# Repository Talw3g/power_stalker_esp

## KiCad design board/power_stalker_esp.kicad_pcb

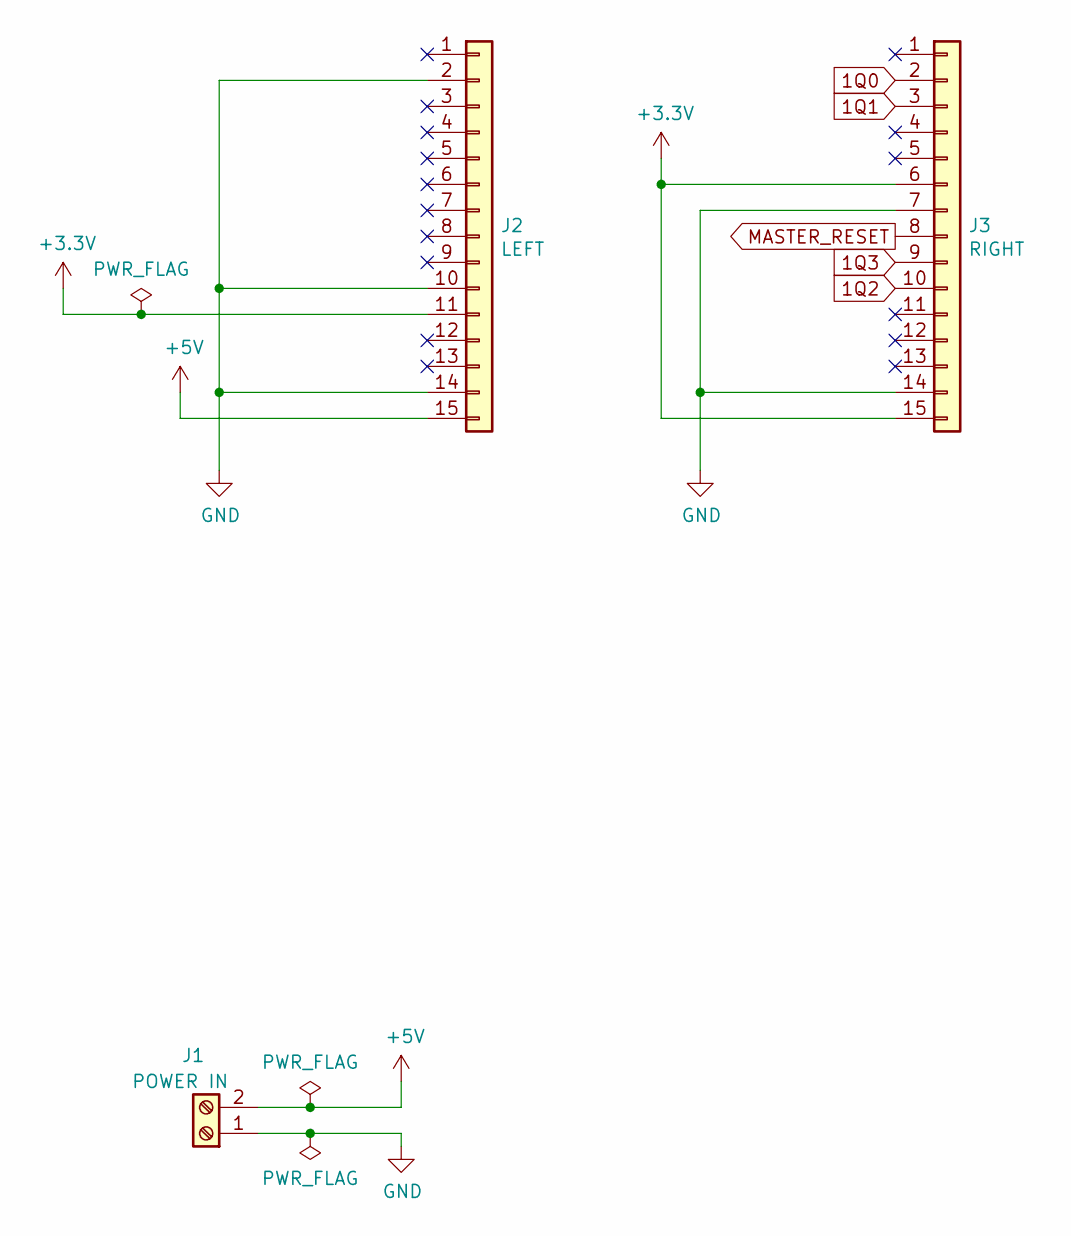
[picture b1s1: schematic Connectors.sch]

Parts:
J1: POWER IN; mpt_0,5-2-2,54; Farnell 3041359
J2: LEFT; PinSocket_1x15_P2.54mm_Vertical; Farnell 2779587
J3: RIGHT; PinSocket_1x15_P2.54mm_Vertical; Farnell 2779587

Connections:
1Q0: J3.2; also elsewhere on the board
1Q1: J3.3; also elsewhere on the board
1Q2: J3.10; also elsewhere on the board
1Q3: J3.9; also elsewhere on the board
+3V3: J2.11, J3.6, J3.15; also elsewhere on the board
+5V: J1.2, J2.15
GND: J1.1, J2.2, J2.10, J2.14, J3.7, J3.14; also elsewhere on the board
MASTER_RESET: J3.8; also elsewhere on the board

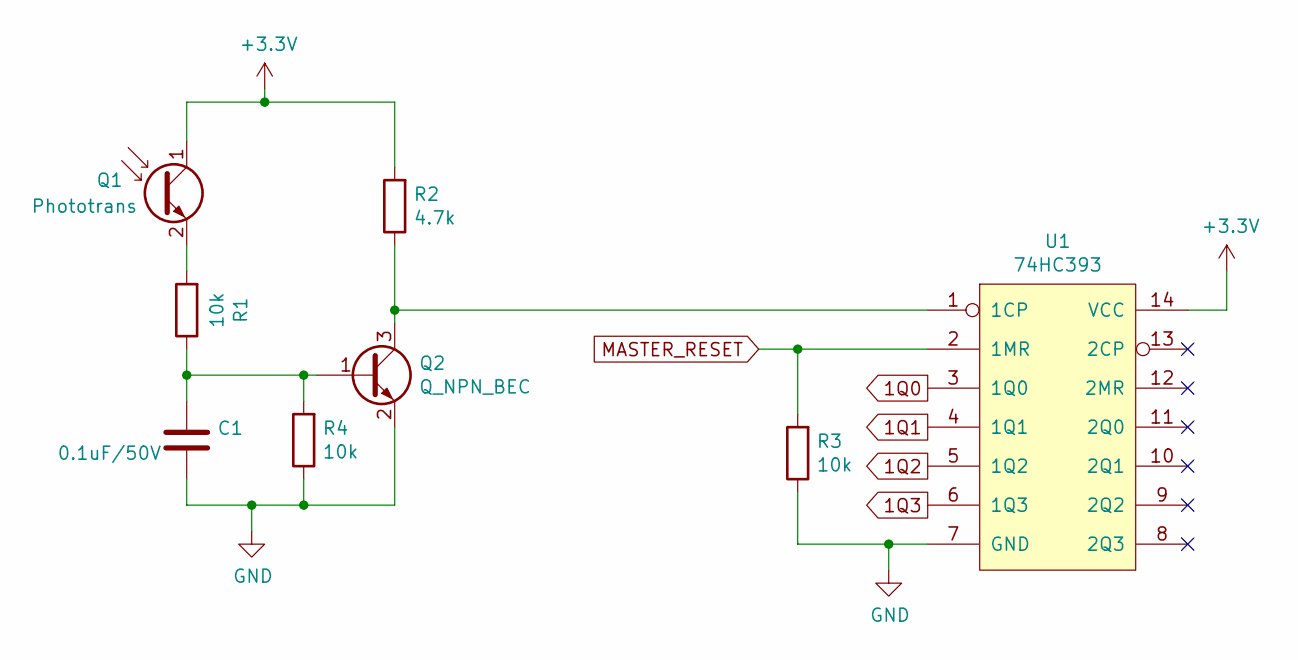
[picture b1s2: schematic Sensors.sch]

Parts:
C1: 0.1uF/50V; C_0603_1608Metric_Pad1.05x0.95mm_HandSolder
Q1: Phototrans; mpt_0,5-2-2,54; Farnell 1497675
Q2: Q_NPN_BEC; SOT-23; Farnell 2464062
R1, R3, R4: 10k; R_0603_1608Metric_Pad1.05x0.95mm_HandSolder
R2: 4.7k; R_0603_1608Metric_Pad1.05x0.95mm_HandSolder
U1: 74HC393; SOIC-14_3.9x8.7mm_P1.27mm; Farnell 1085344

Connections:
1Q0: U1.3 (1Q0); also elsewhere on the board
1Q1: U1.4 (1Q1); also elsewhere on the board
1Q2: U1.5 (1Q2); also elsewhere on the board
1Q3: U1.6 (1Q3); also elsewhere on the board
+3V3: Q1.1 (C), R2.2, U1.14 (VCC); also elsewhere on the board
GND: C1.2, Q2.2 (E), R3.1, R4.1, U1.7 (GND); also elsewhere on the board
MASTER_RESET: R3.2, U1.2 (1MR); also elsewhere on the board
unnamed: C1.1, Q2.1 (B), R1.1, R4.2
unnamed: Q1.2 (E), R1.2
unnamed: Q2.3 (C), R2.1, U1.1 (1CP)

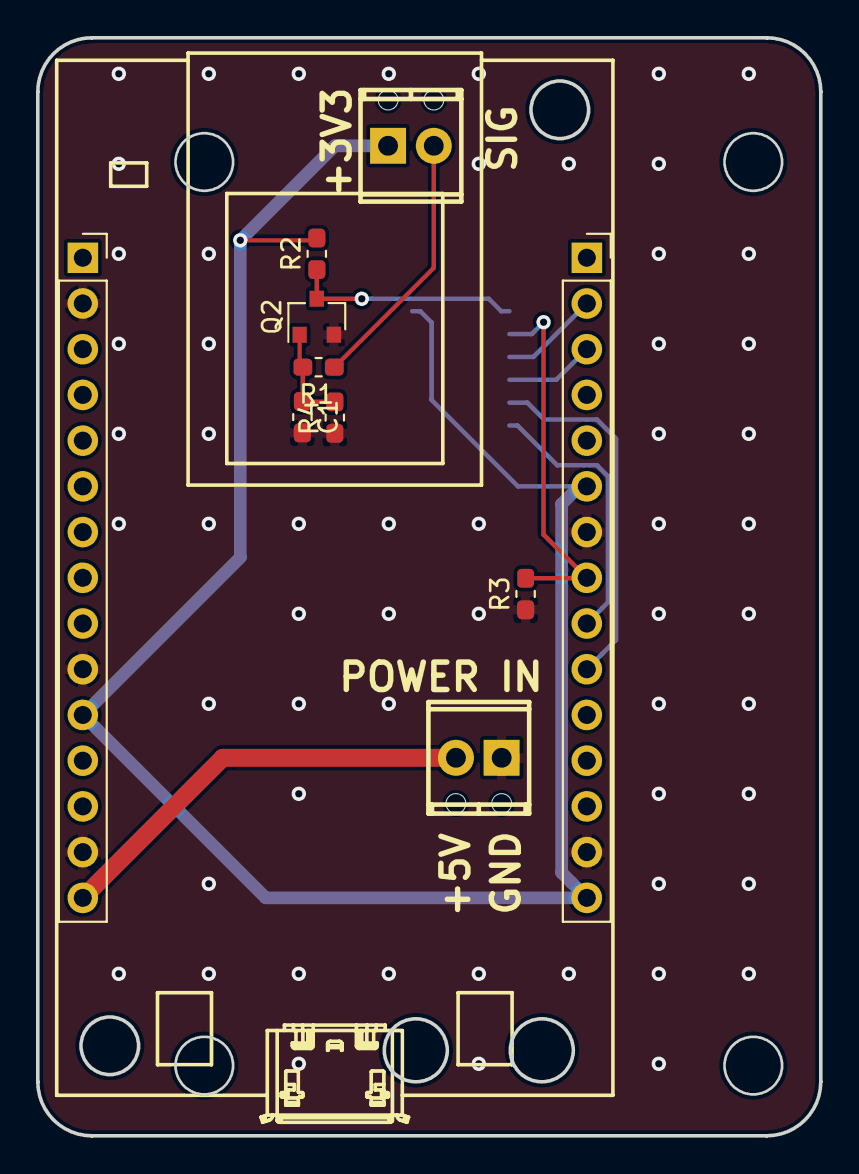
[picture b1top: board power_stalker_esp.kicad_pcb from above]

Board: 2 copper layers, 43.5 x 61.0 mm, 11 parts (1 on the bottom side), 11 nets.

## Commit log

2018-08-10 First commit.
2018-08-12 Fixed double interruption bug.
2018-08-13 Added MQTT message sending.
2018-08-15 finished mqtt support, everything working.
2018-11-08 Reorganized project, initialized board design.
2018-11-09 Routing done.
2018-11-09 Added CAD assembly.
2018-11-09 Generated gerber files.
2018-11-13 Added some farnell refs.
2018-11-13 Updated some refs.
2019-06-30 Updated gitignore
2019-06-30 /!\ Moved some GPIO (D0,D3 and D4 seem to not be real GPIOs...)
2019-07-01 Reworked input circuit.
2020-03-15 Added min time between 2 flashes.
2020-04-14 Corrected server loss bug and NAN power mgmt
2020-04-18 Reworked input circuit (again). Added binary counter bypass.
